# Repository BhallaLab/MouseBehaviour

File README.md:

__Documents__ https://bhallalab.github.io/MouseBehaviour

A C++/Python pipeline to run behavioural experiment.

# Protocols

A protocols must be listed in `./Protocols/BehaviourProtocols.csv`. You must specify the right
protocol code duging cmake configuration. See section __How to run the pipeline__ below.

# How to run the pipeline 

The Arduino uno board and the camera should be connected to the computer before starting the 
session.

## Download and setup (done once) 

This application works __only__ on Ubuntu-18.04 because of the camera firmware available in this repository 
from PointGrey Inc works only with Ubuntu 18.04. 

Install arduino, c++ compiler (gcc), cmake, and boost libraries.

Script `bootstrap.sh` will try to install all dependencies. Required
libraries for PointGrey camera is in the source.
    
    $ git clone  https://github.com/BhallaLab/MouseBehaviour.git
    $ cd MouseBehaviour 
    $ sudo -E ./bootstrap.sh  # If it fails, manual configuration is needed.

Once bootstrap is successful, logout and login. Changes made to your groups comes
into effect only after a fresh login. To verify that you are in appropriate groups, type `groups`
command in terminal. Make sure that `flirimaging` and `dialout` appears in the
group list.

To build and upload to arduino:

    $ mkdir _build 
    $ cd _build
    $ cmake -DANIMAL_NAME=k2 -DSESSION_NUM=1 -DPROTO_CODE=All1 ..
    $ make run              # to run the whole setup, (arduino and camera both must be connected)or
    $ make miniterm         # Just to test arduino board. (camera need to be connected)

On `make run`, a windows will appear with camera feed and couple of plots at the bottom.

## Send commands to arduino

To send commands to arduino, make sure that you focus on the window first (click on it). 

Press `CTRL+C` in terminal to close the session. To see the arduino output in the console,
run `make miniterm`; and press `CTRL+]` to come out of miniterm.

## CMake options

### Port

If you need to change the arduino port, pass `-DPORT=/path/to/port` option to cmake. On a linux system, e.g.

     $ cmake -DPORT=/dev/ttyACM1 -DANIMAL_NAME=k2 -DSESSION_NUM=1 -DPROTO_CODE=A11 ..

## Analysis

Analysis scripts are written in python and requires common numerical computational
framework e.g., `numpy`, `scipy`, `pandas` and additionally `tifflib`.
 
- sudo apt install python-tifflib 

# Commands

- __Puff__ : p
- __Tone__ : t
- __Led__ : l
- __Start__ : s 
- __Shock__ : c
- __Terminate__ : ctrl+c

# What is being printed?

See function `write_data_line` in file `src/main.ino` for updated values.

# How to analyze data

Go to directory `./analysis` and read the `README.md` file there. 

# Extracting arduino data from tiff file.

Each tiff file contains one trial. The first row of each frame contains arduino
data. You can extract that using the script
`./analysis/get_data_line_from_tiff.py` file. 

To extract data run, 

    $ python ./analysis/get_data_line_from_tiff.py /path/to/session/trial01.tiff

It will print the csv files onto the terminal and also save it to a dat file in
the same folder. A plot file is also generated.

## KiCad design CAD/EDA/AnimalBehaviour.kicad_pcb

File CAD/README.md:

# EDA, Electronic Design Automation

This folder contains electrical CAD designs. You'd need kicad version 5 or higher

`.pro` files are kicad files (ask Dilawar).

# CAD, Computer Aided Design

This folder contains 3D cad designs for 3d printing etc. You'd need 
`freecad` or `openscad` to view the designs.

`.stl`, `.scad` can be viewed/edited on FreeCAD or openSCAD (ask Anzal KS).

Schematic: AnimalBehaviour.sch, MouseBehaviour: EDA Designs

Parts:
Assr4ch1: PCB_SSR_4Ch_LLT; 4ChannelSSR
D1: DIODE; D_DO-15_P12.70mm_Horizontal
J1: SSR_INPUT; Molex_KK-254_AE-6410-04A_1x04_P2.54mm_Vertical
J2: SSR OUT; Molex_KK-254_AE-6410-08A_1x08_P2.54mm_Vertical
J3: StimCurrentInject; BarrelJack_CUI_PJ-063AH_Horizontal_CircularHoles
J4: StimIsoIN; Molex_KK-254_AE-6410-02A_1x02_P2.54mm_Vertical
J5: StimIsoIN; BNC_TEConnectivity_1478204_Vertical
J6: Imaging; Molex_KK-254_AE-6410-02A_1x02_P2.54mm_Vertical
J7: CAM; Molex_KK-254_AE-6410-02A_1x02_P2.54mm_Vertical
J8: TONE; Molex_KK-254_AE-6410-02A_1x02_P2.54mm_Vertical
J9: TONE; Jack_3.5mm_CUI_SJ1-3533NG_Horizontal_CircularHoles
J10: JSolenoid; Molex_KK-254_AE-6410-02A_1x02_P2.54mm_Vertical
J11: LED; Molex_KK-254_AE-6410-02A_1x02_P2.54mm_Vertical
J12: Cam; CUI_MD-60SM
J13: Imaging; CUI_MD-60SM
J14: Ext Supp; Molex_KK-254_AE-6410-03A_1x03_P2.54mm_Vertical
Q1: IRF540N; TO-220-3_Horizontal_TabDown
R1: 10M; R_Axial_DIN0309_L9.0mm_D3.2mm_P5.08mm_Vertical
R2, R4: 470E; R_Axial_DIN0309_L9.0mm_D3.2mm_P5.08mm_Vertical
R3: 10K; R_Axial_DIN0309_L9.0mm_D3.2mm_P5.08mm_Vertical
RotaryEncoder1: Orange Optical RotaryEncoder; Molex_KK-254_AE-6410-04A_1x04_P2.54mm_Vertical
ShockPad1: ShockPad; Altech_AK300_1x02_P5.00mm_45-Degree
U1: 4N35; DIP-6_W7.62mm_Socket
XA1: Arduino_Uno_Shield

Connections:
5V: J1.1, RotaryEncoder1.3, XA1.5V1
AGND: J14.3, Q1.3, R3.2
CamTTL: J7.1, J12.2, XA1.D10
DGND: J1.2, J4.1, J5.2, J6.2, J7.2, J8.1, J9.T, J11.2, J12.6, J13.6, RotaryEncoder1.4, U1.2, XA1.GND1
EX_5V: J14.2, U1.5
EX_12V: D1.1, J10.1, J14.1
EncA: RotaryEncoder1.1, XA1.D2
EncB: RotaryEncoder1.2, XA1.D3
ImagingTrig: J6.1, J13.2, XA1.D12
LED: R4.2, XA1.D9
unnamed: D1.2, J10.2, Q1.2
unnamed: J11.1, R4.1
unnamed: Q1.1, R3.1, U1.4
unnamed: R1.1, XA1.D5
unnamed: R2.1, U1.1
OUT+: J2.4, J3.2
OUT-: J2.2, J3.1
PAD+: J2.3, J2.7, ShockPad1.1
PAD-: J2.1, J2.5, ShockPad1.2
Puff: R2.2, XA1.D11
ShockPWM: J2.8, R1.2
ShockRead: J2.6, XA1.A0
ShockRelayCh12: J1.3, XA1.D4
ShockRelayCh34: J1.4, XA1.D6
ShockStimIsolator: J4.2, J5.1, XA1.D7
TONE+: J8.2, J9.S, XA1.D8

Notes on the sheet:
Arduino Uno
Solenoid driver
External supply
Shock Pad Subcircuit
R1 Should Match Paw Resisitance.

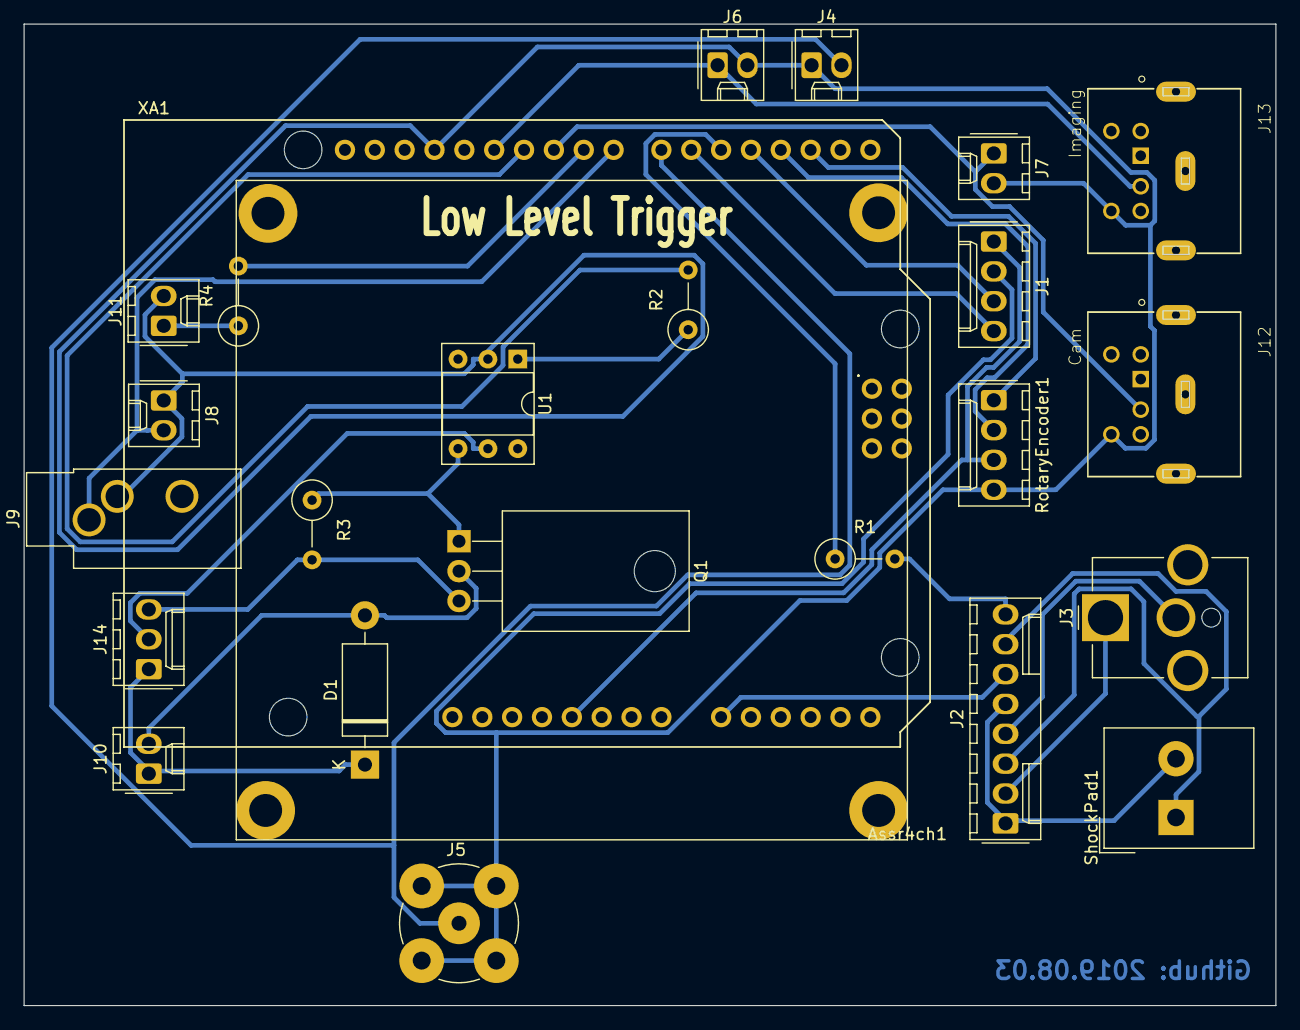
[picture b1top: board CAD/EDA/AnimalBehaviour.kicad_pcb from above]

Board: 2 copper layers, 106.5 x 83.5 mm, 25 parts (0 on the bottom side), 26 nets.

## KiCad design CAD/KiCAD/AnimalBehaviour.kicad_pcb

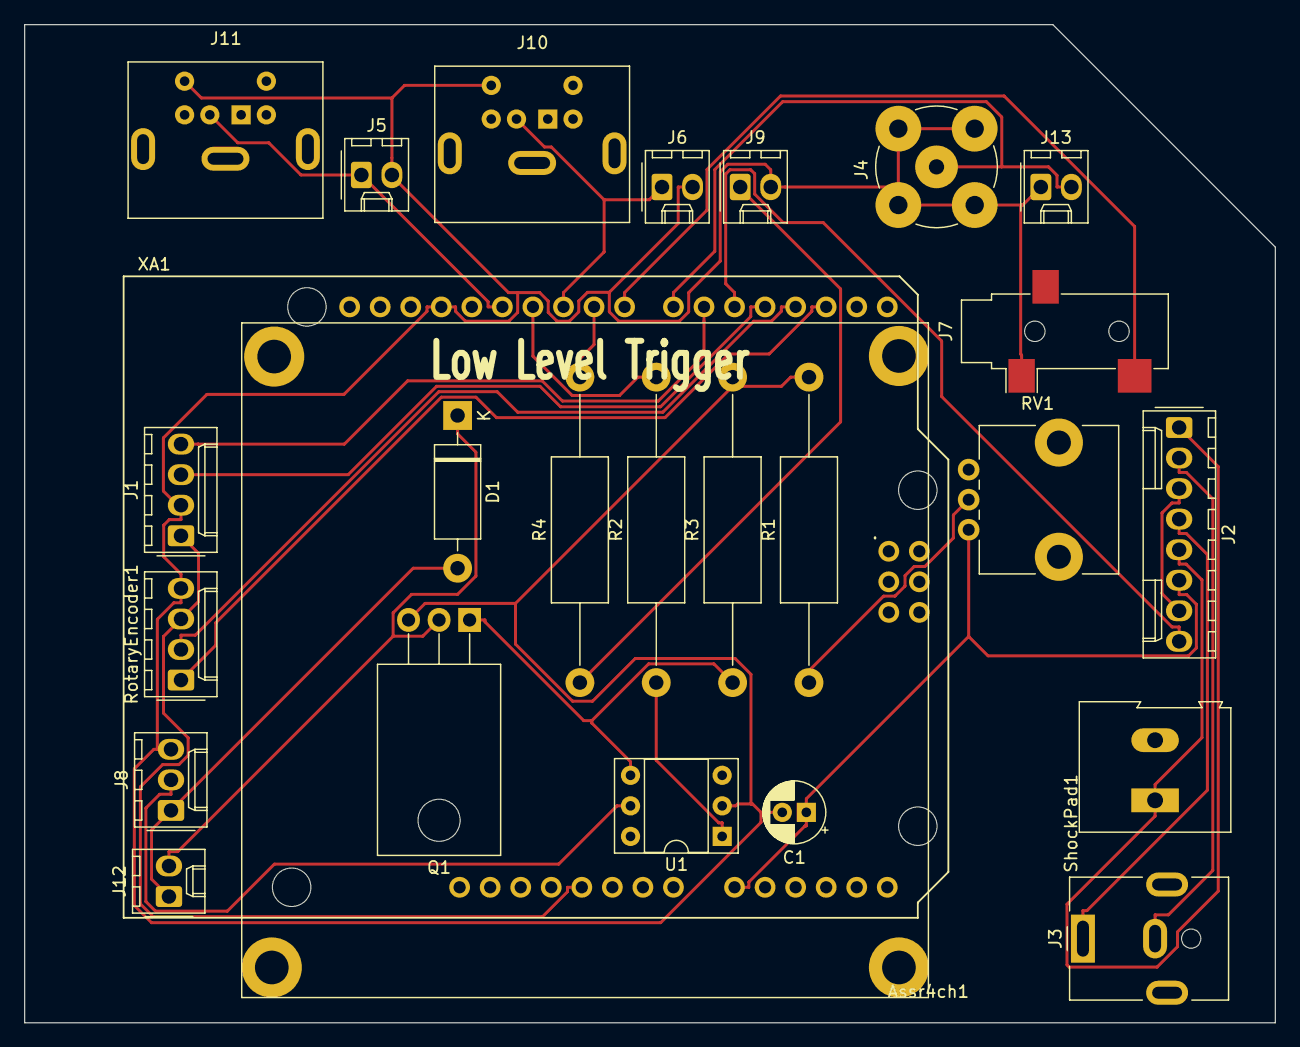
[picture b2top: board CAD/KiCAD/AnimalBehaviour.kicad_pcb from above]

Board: 2 copper layers, 104.0 x 83.0 mm, 26 parts (0 on the bottom side), 25 nets.

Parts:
Assr4ch1: PCB_SSR_4Ch_LLT; 4ChannelSSR
C1: 47nF; CP_Radial_D5.0mm_P2.00mm
D1: DIODE; D_DO-15_P12.70mm_Horizontal
J1: SSR_INPUT; Molex_KK-254_AE-6410-04A_1x04_P2.54mm_Vertical
J2: SSR OUT; Molex_KK-254_AE-6410-08A_1x08_P2.54mm_Vertical
J3: StimCurrentInject; BarrelJack_CUI_PJ-063AH_Horizontal
J4: StimIsoIN; BNC_TEConnectivity_1478204_Vertical
J5: ImagingTrig; Molex_KK-254_AE-6410-02A_1x02_P2.54mm_Vertical
J6: CAM; Molex_KK-254_AE-6410-02A_1x02_P2.54mm_Vertical
J7: AudioJack2; Jack_3.5mm_CUI_SJ-3523-SMT_Horizontal
J8: Conn_01x03_Male; Molex_KK-254_AE-6410-03A_1x03_P2.54mm_Vertical
J9: LED; Molex_KK-254_AE-6410-02A_1x02_P2.54mm_Vertical
J10: Cam; Connector_Mini-DIN_Female_6Pin_2rows
J11: Imaging; Connector_Mini-DIN_Female_6Pin_2rows
J12: Conn_01x02_Male; Molex_KK-254_AE-6410-02A_1x02_P2.54mm_Vertical
J13: StimIsoIN; Molex_KK-254_AE-6410-02A_1x02_P2.54mm_Vertical
Q1: IRF540N; TO-220-3_Horizontal_TabDown
R1: 1K; R_Axial_DIN0414_L11.9mm_D4.5mm_P25.40mm_Horizontal
R2, R4: 470E; R_Axial_DIN0414_L11.9mm_D4.5mm_P25.40mm_Horizontal
R3: 10K; R_Axial_DIN0414_L11.9mm_D4.5mm_P25.40mm_Horizontal
RV1: 1 MegOhm; Potentiometer_Alps_RK09L_Single_Vertical
RotaryEncoder1: Orange Optical RotaryEncoder; Molex_KK-254_AE-6410-04A_1x04_P2.54mm_Vertical
ShockPad1: ShockPad; TerminalBlock_Altech_AK300-2_P5.00mm
U1: 4N35; DIP-6_W7.62mm_Socket
XA1: Arduino_Uno_Shield

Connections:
5V: J1.1, RotaryEncoder1.3, XA1.5V1
AGND: C1.2, J1.2, J4.2, J5.2, J6.2, J7.S, J8.3, J9.2, J10.6, J11.6, J13.1, Q1.3, R1.2, R3.2, RotaryEncoder1.4, U1.2, XA1.GND1
CamTTL: J6.1, J10.2, XA1.D10
EX_5V: J8.2, U1.5
EX_12V: D1.2, J8.1, J12.1
EncA: RotaryEncoder1.1, XA1.D2
EncB: RotaryEncoder1.2, XA1.D3
ImagingTrig: J5.1, J11.2, XA1.D12
LED: R4.2, XA1.D9
unnamed: D1.1, J12.2, Q1.2
unnamed: J9.1, R4.1
unnamed: Q1.1, R3.1, U1.4
unnamed: R1.1, RV1.2
unnamed: R2.1, U1.1
OUT+: J2.4, J3.1
OUT-: J2.2, J3.2
PAD+: J2.3, J2.7
PAD-: J2.1, J2.5, ShockPad1.1
Puff: R2.2, XA1.D11
ShockPWM: J2.8, XA1.D5
ShockRead: C1.1, J2.6, RV1.1, XA1.A0
ShockRelayCh12: J1.3, XA1.D4
ShockRelayCh34: J1.4, XA1.D6
ShockStimIsolator: J4.1, J13.2, XA1.D7
TONE+: J7.T, XA1.D8

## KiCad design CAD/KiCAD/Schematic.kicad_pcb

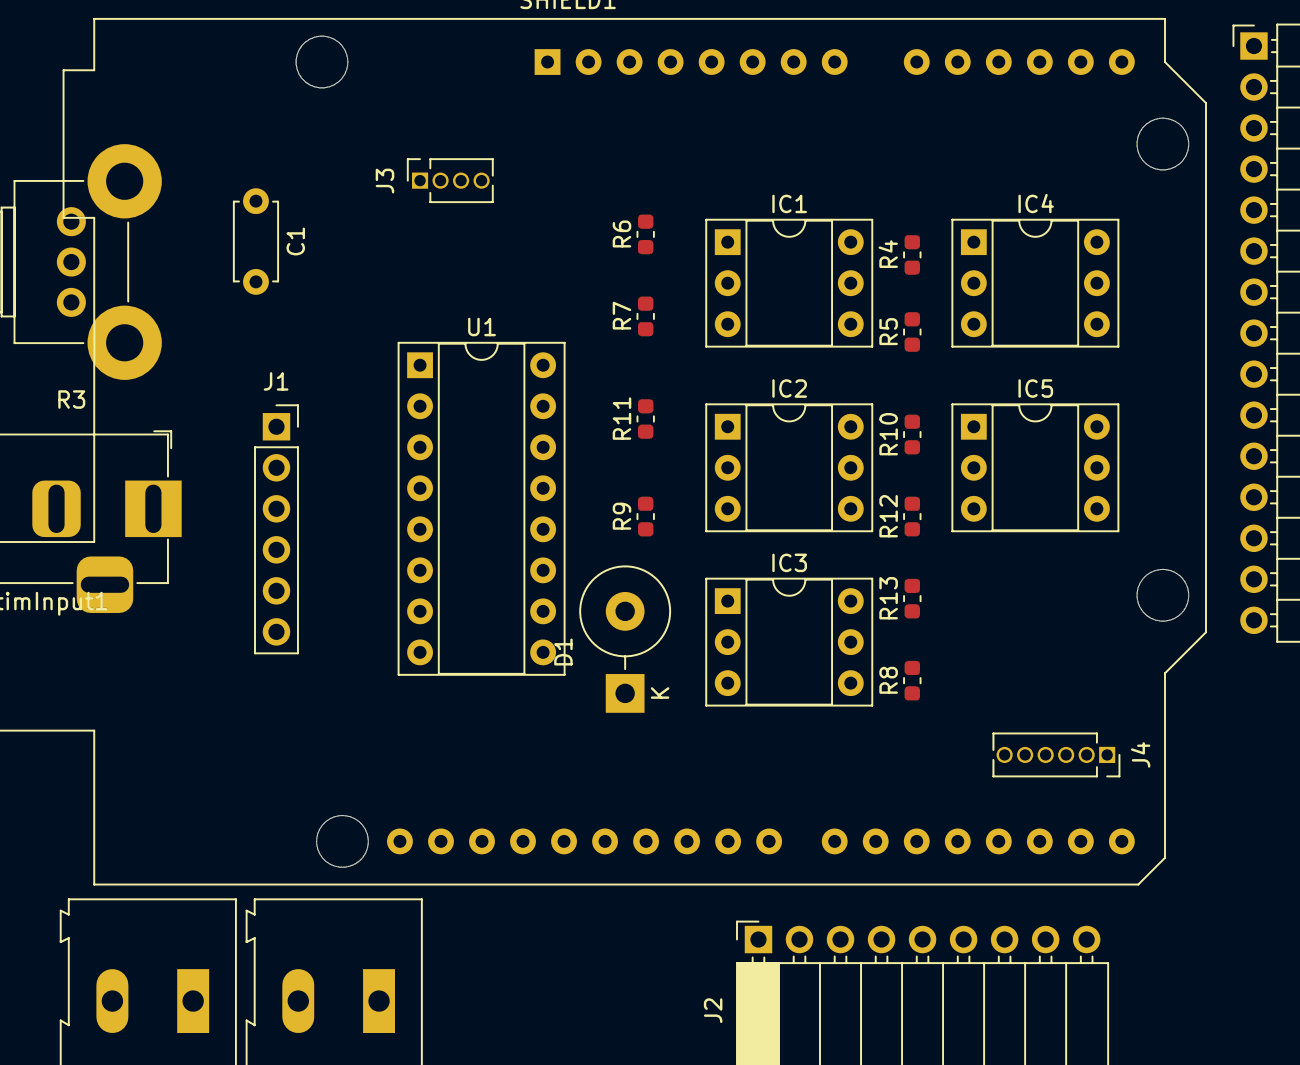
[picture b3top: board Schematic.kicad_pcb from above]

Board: 2 copper layers, 28 parts (0 on the bottom side), 34 nets, no tracks yet.

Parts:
C1: 47 uF; C_Disc_D4.7mm_W2.5mm_P5.00mm
CN1: OutputPad; PinHeader_1x15_P2.54mm_Horizontal
D1: DIODE; D_DO-27_P5.08mm_Vertical_KathodeUp
IC1, IC2, IC3, IC4, IC5: 4N35; DIP-6_W7.62mm_Socket
J1: SSR-ToInput; PinSocket_1x06_P2.54mm_Vertical
J2: SSR-ToOutput; PinSocket_1x09_P2.54mm_Horizontal
J3: RotaryEncoder; PinSocket_1x04_P1.27mm_Vertical
J4: AnalogIn; PinSocket_1x06_P1.27mm_Vertical
J-InStimInput1: 90V; BarrelJack_Horizontal
JPad1: ShockPad; TerminalBlock_Altech_AK300-2_P5.00mm
JPad2: StimInput; TerminalBlock_Altech_AK300-2_P5.00mm
R3: 1M; Potentiometer_Alps_RK09K_Single_Horizontal
R4, R10, R12: 560E; R_0603_1608Metric
R5, R6: 470E; R_0603_1608Metric
R7, R8, R9, R11, R13: 15k; R_0603_1608Metric
SHIELD1: ARDUINO_SHIELD; Arduino_UNO_R3_WithMountingHoles
U1: ULN2003A; DIP-16_W7.62mm_Socket

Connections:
5V: J1.1, J3.3
12 V: CN1.11, D1.1
A0: C1.1, J2.6, J4.1, R3.1
AGND: C1.2, CN1.1, CN1.10, CN1.12, CN1.14, J3.4, R3.2, R7.1, R8.2, R9.2, R11.2, R13.2, U1.8
D2: J3.1, SHIELD1.2
D3: J3.2, SHIELD1.3
D4: J1.3, J1.4, SHIELD1.4
D5: J2.8, SHIELD1.5
D6: J1.5, J1.6, SHIELD1.6
D7: JPad2.1, SHIELD1.7
D8: R12.1, SHIELD1.8
D9: R10.1, SHIELD1.9
D11: R5.1, SHIELD1.11
D12: R6.1, SHIELD1.12
D13: R4.1, SHIELD1.13
DGND: IC1.2, IC2.2, IC3.2, IC4.2, IC5.2, J1.2, JPad2.2
EX 5 V: CN1.9, IC1.5, IC2.5, IC3.5, IC4.5, IC5.5
unnamed: IC1.1, R4.2
unnamed: IC2.1, R5.2
unnamed: IC3.1, R6.2
unnamed: IC4.1, R10.2
unnamed: IC5.1, R12.2
unnamed: J2.1, J2.5, JPad1.2
unnamed: J2.3, J2.7, JPad1.1
unnamed: J2.2, J-InStimInput1.1
unnamed: J2.4, J-InStimInput1.2
Solenoid1_1: CN1.6, CN1.8, D1.2, U1.9
Solenoid1_2: CN1.7, U1.15
Solenoid2_2: CN1.5, U1.16
Tone1: CN1.15, IC4.4, R11.1
Tone2: CN1.13, IC5.4, R13.1
Tone3: CN1.2, IC1.4, R7.2
ULN_IN1: IC2.4, R9.1, U1.1
ULN_IN2: IC3.4, R8.1, U1.2

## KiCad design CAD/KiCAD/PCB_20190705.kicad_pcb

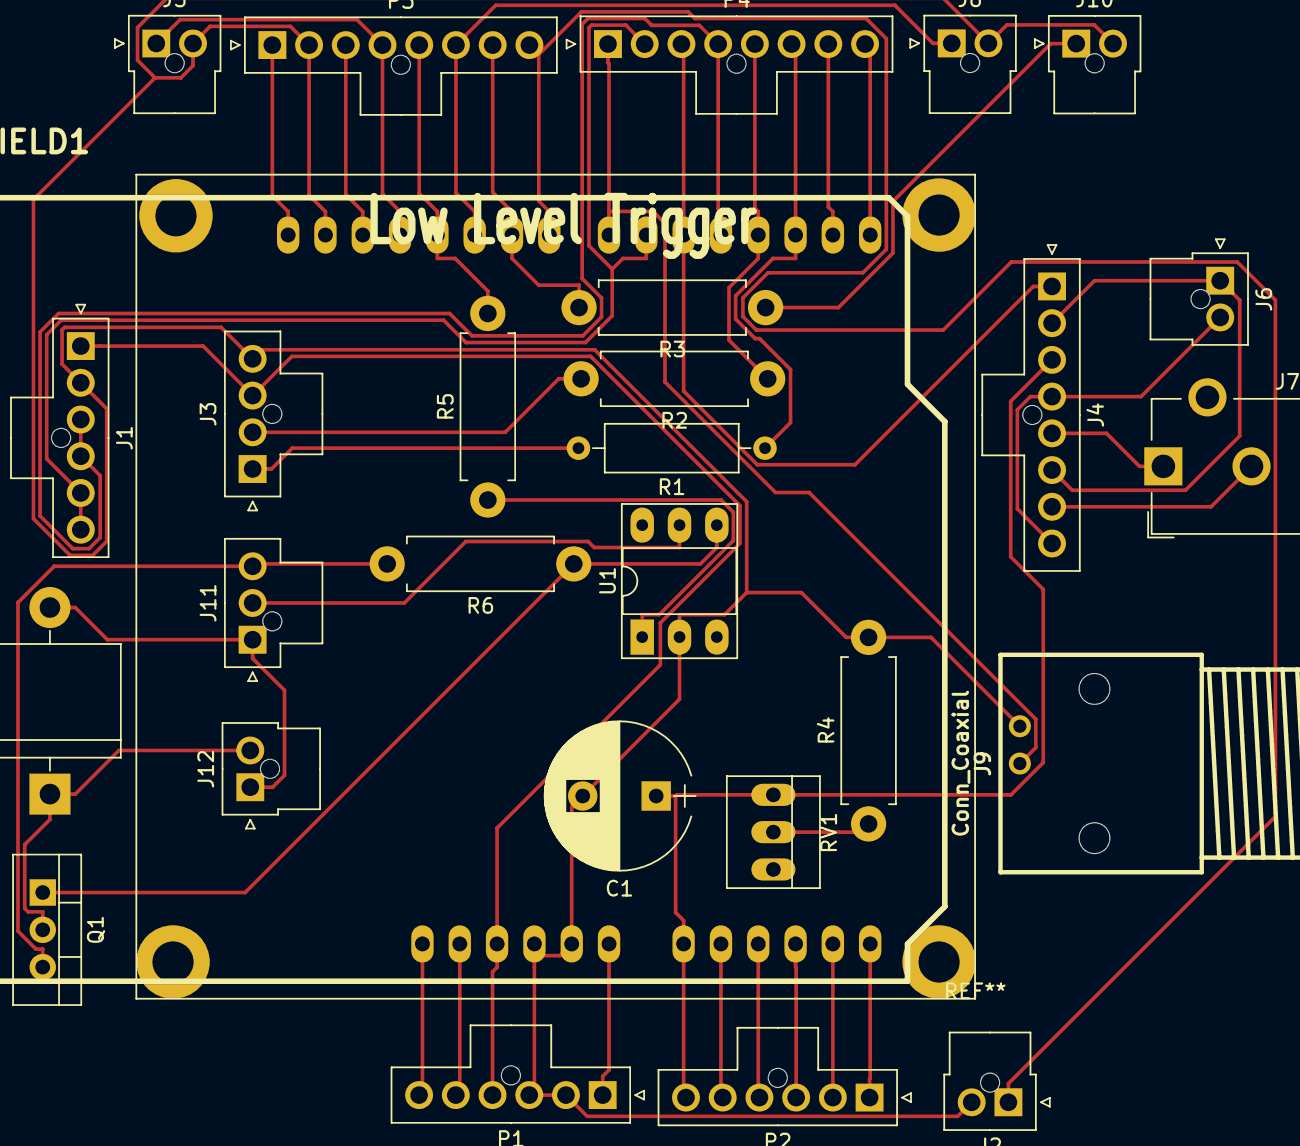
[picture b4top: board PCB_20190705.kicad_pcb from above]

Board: 2 copper layers, 28 parts (0 on the bottom side), 40 nets.

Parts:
C1: 47nF; CP_Radial_D10.0mm_P5.00mm
D1: DIODE; D_5KP_P12.70mm_Horizontal
J1: Conn_01x06_Male; Molex_NanoFit_1x06x2.50mm_Straight
J2, J5, J6, J8, J10, J12: Conn_01x02_Male; Molex_NanoFit_1x02x2.50mm_Straight
J3: Conn_01x04_Male; Molex_NanoFit_1x04x2.50mm_Straight
J4: Conn_01x08_Male; Molex_NanoFit_1x08x2.50mm_Straight
J7: Jack-DC; Barrel_Jack_CUI_PJ-102AH
J9: Conn_Coaxial; bnc_90_1-1337543-0
J11: Conn_01x03_Male; Molex_NanoFit_1x03x2.50mm_Straight
P1, P2: CONN_6; Molex_NanoFit_1x06x2.50mm_Straight
P3, P4: CONN_8; Molex_NanoFit_1x08x2.50mm_Straight
Q1: IRF540N; TO-220-3_Vertical
R1: 560E; R_Axial_DIN0309_L9.0mm_D3.2mm_P12.70mm_Horizontal
R2: 560E; R_Axial_DIN0411_L9.9mm_D3.6mm_P12.70mm_Horizontal
R3, R5: 470E; R_Axial_DIN0411_L9.9mm_D3.6mm_P12.70mm_Horizontal
R4: 1K; R_Axial_DIN0411_L9.9mm_D3.6mm_P12.70mm_Horizontal
R6: 10K; R_Axial_DIN0411_L9.9mm_D3.6mm_P12.70mm_Horizontal
RV1: 1 MegOhm; PINHEAD1-3
SHIELD1: ARDUINO_SHIELD; ARDUINO_SHIELD_040pins
U1: 4N35; DIP-6_W7.62mm_Socket_LongPads

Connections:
3V3: P1.5, SHIELD1.3V3
5V: J1.1, J3.3, P1.4, SHIELD1.5V
A0: C1.1, J4.3, P2.6, RV1.1, SHIELD1.AD0
A1: P2.5, SHIELD1.AD1
A2: P2.4, SHIELD1.AD2
A3: P2.3, SHIELD1.AD3
A4: P2.2, SHIELD1.AD4
A5: P2.1, SHIELD1.AD5
AGND: J11.3, Q1.3, R6.2
AREF: P3.1, SHIELD1.AREF
D0: P4.8, SHIELD1.0
D1: P4.7, SHIELD1.1
D2: P4.6, R1.1, SHIELD1.2
D3: P4.5, R2.1, SHIELD1.3
D4: J1.3, J1.4, P4.4, SHIELD1.4
D5: J4.1, P4.3, SHIELD1.5
D6: J1.5, J1.6, P4.2, SHIELD1.6
D7: J9.1, P4.1, SHIELD1.7
D8: J2.1, P3.8, SHIELD1.8
D9: P3.7, R3.2, SHIELD1.9
D10: J8.1, P3.6, SHIELD1.10
D11: P3.5, R5.2, SHIELD1.11
D12: J5.1, P3.4, SHIELD1.12
D13: P3.3, SHIELD1.13
DGND: C1.2, J1.2, J2.2, J3.4, J5.2, J8.2, J9.2, J10.2, P1.2, P1.3, P3.2, R4.2, SHIELD1.GND1, SHIELD1.GND2, SHIELD1.GND3, U1.2
EX_5V: J11.2, U1.5
EX_12V: D1.2, J11.1, J12.1
unnamed: D1.1, J12.2, Q1.2
unnamed: J3.1, R1.2
unnamed: J3.2, R2.2
unnamed: J10.1, R3.1
unnamed: Q1.1, R6.1, U1.4
unnamed: R4.1, RV1.2
unnamed: R5.1, U1.1
OUT+: J4.5, J7.1
OUT-: J4.7, J7.2
PAD+: J4.2, J4.6, J6.1
PAD-: J4.4, J4.8, J6.2
RST: P1.6, SHIELD1.RST
V_IN: P1.1, SHIELD1.V_IN

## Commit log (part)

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2018-01-02 Without LATEX.
2018-03-27 Without LATEX.
    O1 sets camera ttl pulse up and 2 brings it down. Works only before 's' is pressed.
    Craete backup while copyong.
    Added legal commands.
    integrated command 1 and 2.
    1-> start camera
    2->stop camera.
2018-03-29 use command 1 and 2.
2018-03-31 May be later.
    Former-commit-id: 9242eaf0ce55b5b240dfa1c70a2b06db213e1ca2
2018-05-05 Per microsecond. Mouse may not return microsecond precision.
2018-05-24 Both trial types are now separated.
2018-06-07 Some more fixes.
2018-06-07 each trial also get speed vector plotted.
2018-11-06 Added instructions to generate summary plot.
2018-11-29 INtegrated.
2018-11-30 Closes #21. Last two columns are related to rotary encoder.
    - Second last: Value of rotary encoder i.e. total steps (+/-)
    - Last: angular velocity in `radian/sec` .
2018-12-08 Updated scripts and readme. Fixed SESSION_TYPE in readme.
2018-12-11 Integrated but havn't tested yet.
2018-12-11 Tiny tweaks.
2018-12-11 Script to plot protocols.
2018-12-11 Convert given protocol from CSV file to config file.
2018-12-11 Updated a little bit more.
2018-12-11 Added protocol.h file which is generated by cmake and python script.
2018-12-12 Increased baud rate to make sure we can transmit 100 chars per 10ms.
2018-12-12 Needs testing.
2018-12-12 Send a PR with comments.
2018-12-12 Added travis CI.
2018-12-12 Added badge [skip ci].
2018-12-12 Default protocol file for testing on travis.
    Added boost to dependencies.
2018-12-12 ffmpeg to dependencies as well.
2018-12-14 SESSION_TYPE is renamed to CS_TYPE.
    Removed mouse server.
    More cleanup of mouse related changes.
    Minor tweaks. Still not connecting to camera server.
    Some refactoring.
    Fixed baudRate bug. Now cmake sets this value everywhere.
2018-12-14 Fixed baudrate issue.
2018-12-21 Updated SDK.
2018-12-21 Squashed commit of the following:
    commit 8396ab4e7035b09d30174268df4bb285ac6b60b9
    Author: Dilawar Singh <dilawars@ncbs.res.in>
    Date: Fri Dec 21 10:04:38 2018 +0530
    Updated SDK.
2018-12-21 Minor tweaks should work fine.
2018-12-21 Small correction in camera pin read.
2019-01-26 Script to convert abf to images or csv files.
2019-01-26 Python3.5 compatible.
    Python2/3 compatible.
2019-02-04 only csv file format is supported in directory mode.
2019-02-28 Today's commit.
2019-02-28 trying python3.
2019-02-28 Python3 support is final.
2019-03-02 Changes related to unicode.
2019-03-05 Updated protocols. needs testing.
2019-03-05 Devel (#29)
    * Updated protocols. needs testing.
    * Probably all cases are implemented.
    * Seems to be working fine (human check).
2019-03-05 Seems to be working fine (human check).
2019-03-05 Added dataline from the arduino.
2019-03-05 Now I can write to image.
2019-03-05 Added program options.
2019-03-05 Updated a bit more.
2019-03-05 Cool. Almost complete.
2019-03-05 Almost over.
2019-03-05 Show every 10th frame.
2019-03-05 Don't write 0th trial.
2019-03-05 Added libtiff and libserial development libraries.
2019-03-06 Enabled drawing rectangle.
2019-03-06 Write camera status to mainline.
2019-03-06 Fixed ITI interval issue.
2019-03-06 Slow sampling in POST.
2019-03-06 Increased delay in POST.
2019-03-10 renamed target and add classifier.
2019-03-10 Fixed seg-fault.
2019-03-11 If -o option is given, plot the points.
2019-03-11 updated with lower x limit.
2019-03-12 Colormap is viridis.
2019-03-12 Updated instructions.
2019-03-12 Deleted socket file.
2019-03-12 Run boostrap on travis.
2019-03-12 more dependencies.
2019-03-12 install python3-pip as well.
2019-03-12 Added libserial-dev to dependencies on travis.
2019-03-12 Some more update.
2019-03-12 Use two processes.
2019-03-20 Simple pulse train generator in arduino.
2019-03-21 track issue #33.
2019-03-21 Bit more update #33.
2019-03-26 Issue33 (#36)
    * track issue #33.
    * Bit more update #33.
    * Modified.
2019-04-08 Added new protocls incorporating shock
2019-04-10 Use LIGHT instead of LED.
2019-06-04 create a subfolder (timestamp as name) if the DATAFDIR already exsits. Close #43 .
2019-06-04 Few more chages [skip ci]
2019-06-04 Added libboost as dependencies.
    Fixes to README.md
2019-06-04 Added new protocls incorporating shock (#39)
    * Update BehaviourProtocols.csv
    new tral comit
    * Added new protocls incorporating shock
2019-06-04 Building fine. using timer1 instead of 2 which is used by counter.
2019-06-04 Needs for testing.
2019-06-04 Issue44 (#45)
    * Integration of shock.
    * Building fine. using timer1 instead of 2 which is used by counter.
    * Not working very nicely.
    * Needs for testing.
2019-06-05 1200 rising edges in 1 rotation. (#46)
2019-06-08 digitalAttachInterrupt not found.
2019-06-10 imaging camera shutter delayed for 60ms for each trial.
2019-06-11 How stupid of me. Raise error when file exists. Start trial from 1. Fixes #41
2019-06-11 Use digitalInterrupt code. Upgrade arduino.
2019-06-11 Attaching interrupts with correct numbers. PIN 2 --> 0 and PIN 3 --> 1.
2019-06-27 Needs input from Upi.
2019-06-27 Timer1 has callback. Every 1ms it gets called. Every 50 steps, we switch on the stim and next 50 step, we readout from arduino.
2019-06-27 Updated.
2019-06-28 Squashed 'Arduino/TimerOne/' content from commit 0f2d2d9
    git-subtree-dir: Arduino/TimerOne
    git-subtree-split: 0f2d2d9895648ecdfed3c890c03684bf0c245cf7
2019-06-29 Fixed script to draw position and speed from arduino data.
2019-06-30 Added KiCad project.
2019-06-30 Needs to update the ciruit etc.
2019-06-30 Almost complete.
2019-07-02 Added RC tank to get the RMS value. R=1.2 MOhm C=47 nF. Tau ~50mS
2019-07-02 final testing tomorrow. Can't focus anymore.
2019-07-03 cmake finds boost thread.
2019-07-03 Added shock line plot.
2019-07-03 Cool. Colored picture.
2019-07-03 Still need to debug.
2019-07-04 Added CAD design schematic in PDF.
2019-07-04 Added readme files with design.
2019-07-04 Using A0 instead of A3 now.
2019-07-04 Passing electrical rules.
2019-07-04 refactoring.
2019-07-04 reassigned PCB components.
2019-07-04 dsn file for freelayout tool.
2019-07-04 updated pcb. Single copper layer.
2019-07-05 Added sym-lib-table which tells which library to load.
2019-07-05 PCB is renamed to conform to project name.
2019-07-05 Update .gitignore
    gitignore file.
2019-07-05 redundant folder.
2019-07-05 Added final design.
2019-07-06 ERC passed with assign PWR_FLAGS. See this for more information https://forum.kicad.info/t/errtype-3-pin-connected-to-some-others-pins-but-no-pin-to-drive-it/10946/4
2019-07-06 v2019.07.06.alpha1
2019-07-06 Archives and other updates.
2019-07-06 Some updates to README files.
2019-07-06 Tag this version and release.
2019-07-06 Removed old files.
2019-07-06 Need opensuse.
2019-07-07 Needs to update 3d model.
2019-07-07 Version 20190707.pre1
2019-07-07 Aligned some components properly.
2019-07-08 Fixed issues raised by @mrdorababu in #52.
2019-07-08 replaced oval holes with circular holes.
2019-07-08 temp commit.
2019-07-08 Layout is autocomputed.
2019-07-09 Rearragenment of components. Shock related components on the bottom edge.
2019-07-09 version 2019.07.09
2019-07-11 Updated readme with instuctions to generate data.
2019-07-11 fixed #54.
2019-07-12 added profile img.
2019-07-12 individual plot is done.
2019-07-13 update.
2019-07-14 Summary plot is generated.
2019-07-14 Create docker file for posterity.
2019-07-14 Docker file.
2019-07-14 Build successful.
2019-07-14 updated bit more [skip ci]
2019-07-14 Renamed.
2019-07-14 [skip ci] temp commit.
2019-07-14 Build configuration.
2019-07-15 Added build options.
2019-07-15 Small update.
2019-07-15 root rocks.
2019-07-15 Upload this image.
2019-07-16 Set theme jekyll-theme-slate
2019-07-16 Updated dockerfile for running the behaviour experiment.
2019-07-16 2/3 of screen is used.
2019-07-16 Renames and removed empty files.
2019-07-16 fixed paths for travis.
2019-07-16 Added mkdocs build syste for ghpages.
2019-07-16 Added document URL.
2019-07-16 Use python3.6 .
2019-07-16 Deployed 76fde4e with MkDocs version: 1.0.4
2019-07-16 Updated docs.
2019-07-16 Updated docker image a bit more.
2019-07-16 Deployed ff5aa9e with MkDocs version: 1.0.4
2019-07-16 Added readthedocs config files.
2019-07-17 needs to write GUI.
2019-07-17 Supports 13, 14, and 15 fields csv from arduino.
2019-07-17 Fixed interpolation bug.
2019-07-18 removed emoji.
2019-08-02 Works fine with breadboard.
2019-08-02 Updated PCB version 2019.08.02
2019-08-02 Sampling shock pad at 1k.
2019-08-06 Fixes the shock value plotting. Dual plotting in roi (not sure why? yet).
2019-08-07 Updated docker image and added fixes to gui.
    - Docker was not launching.
    - There is no need to clone repo. Docker is launched from repo so use a
    local copy.
    - Dokcker uses its own build dir `_docker_build`.
    - GUI needs to know this directory. Added an argument --build-dir;
    before this directory was hard codeded.
2019-08-08 Pinning some module version. #60.
2019-08-09 update to docker image - install xdg-open Fixes to GUI. - problem in automatically updating data-dir (not resolved yet)
2019-09-24 Script generating protocol file now.
2019-09-24 Do the rest tomorrow.
2019-09-25 Added methods.
2019-09-26 overlap.
2019-09-26 Almost done with simpler version as explained in https://github.com/BhallaLab/MouseBehaviour/issues/61#issuecomment-535355048. Related to #61
2019-10-04 Some changes, needs some fixes.
2019-12-17 Script to compute latecy in recordings.
2019-12-17 Added labels on histogram.
2020-07-21 create all missing directories.
2020-07-21 install missing dependencies
2020-08-21 Upgraded to 18.04
2020-08-25 Bump pillow from 6.1.0 to 7.1.0
    Bumps [pillow](https://github.com/python-pillow/Pillow) from 6.1.0 to 7.1.0.
    - [Release notes](https://github.com/python-pillow/Pillow/releases)
    - [Changelog](https://github.com/python-pillow/Pillow/blob/master/CHANGES.rst)
    - [Commits](https://github.com/python-pillow/Pillow/compare/6.1.0...7.1.0)
2021-06-08 Bump pillow from 6.1.0 to 8.2.0
    Bumps [pillow](https://github.com/python-pillow/Pillow) from 6.1.0 to 8.2.0.
    - [Release notes](https://github.com/python-pillow/Pillow/releases)
    - [Changelog](https://github.com/python-pillow/Pillow/blob/master/CHANGES.rst)
    - [Commits](https://github.com/python-pillow/Pillow/compare/6.1.0...8.2.0)
    ---
    updated-dependencies:
2021-09-08 Bump pillow from 6.1.0 to 8.3.2
    Bumps [pillow](https://github.com/python-pillow/Pillow) from 6.1.0 to 8.3.2.
    - [Release notes](https://github.com/python-pillow/Pillow/releases)
    - [Changelog](https://github.com/python-pillow/Pillow/blob/master/CHANGES.rst)
    - [Commits](https://github.com/python-pillow/Pillow/compare/6.1.0...8.3.2)
    ---
    updated-dependencies:
2022-03-11 Bump pillow from 6.1.0 to 9.0.1
    Bumps [pillow](https://github.com/python-pillow/Pillow) from 6.1.0 to 9.0.1.
    - [Release notes](https://github.com/python-pillow/Pillow/releases)
    - [Changelog](https://github.com/python-pillow/Pillow/blob/main/CHANGES.rst)
    - [Commits](https://github.com/python-pillow/Pillow/compare/6.1.0...9.0.1)
    ---
    updated-dependencies:
